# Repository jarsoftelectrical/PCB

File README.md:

# PCB
PCB files for various projects

Some of these have not been prototyped and may have faults, use at your own risk.

Created with Eagle CAD  full version, any changes please share back to me.

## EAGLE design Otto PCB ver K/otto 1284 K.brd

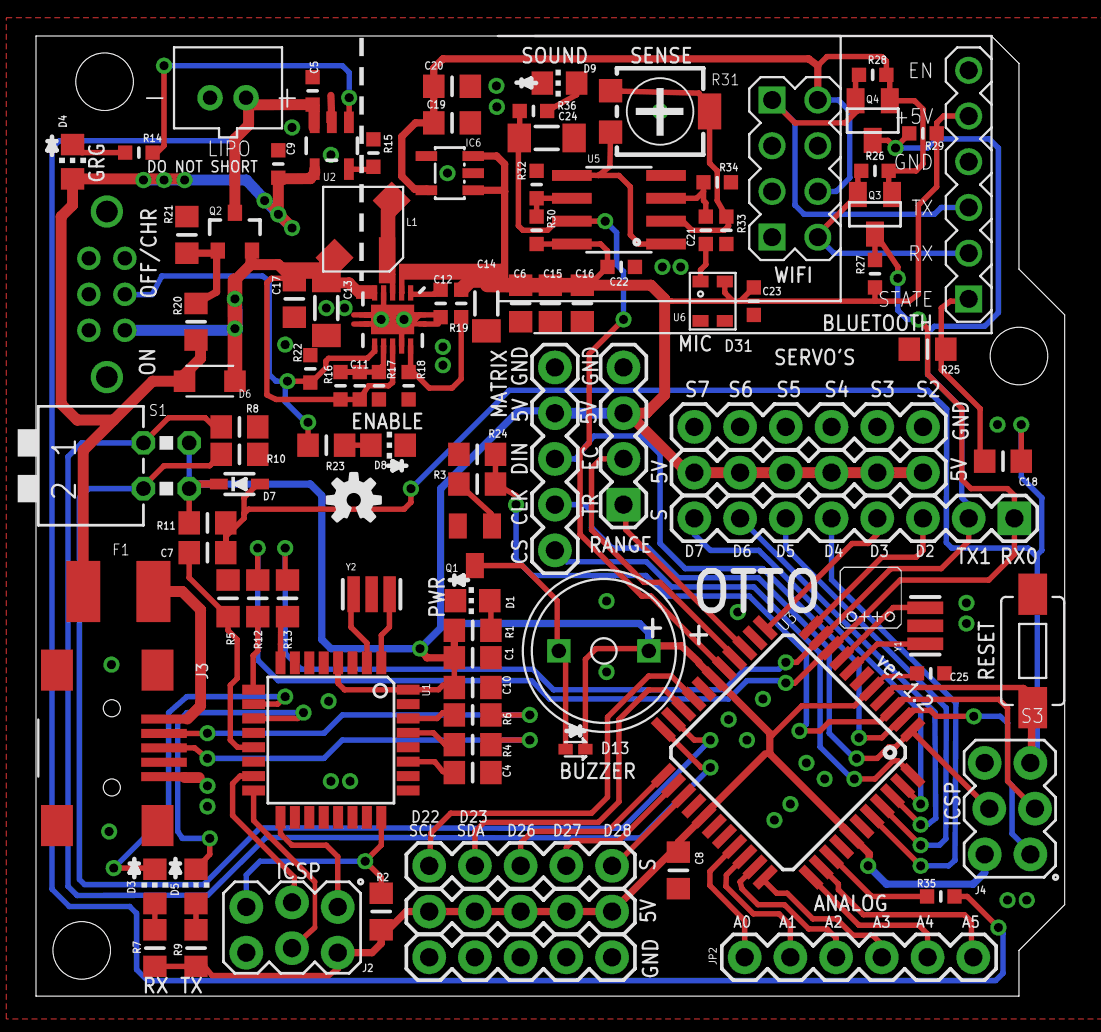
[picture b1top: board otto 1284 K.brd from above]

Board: 2 copper layers, 57.2 x 53.3 mm, 104 parts (0 on the bottom side), 79 nets.

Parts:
C1, C7, C8, C10, C18, C20: 0.1u; C0805MP
C4: 1u; C0805MP
C5, C9: 4.7uF; C0603MP
C6, C15, C16, C17, C19: 22uF; C0805MP
C11, C12, C21: 0.1uF; C0603MP
C13, C14, C24: 10uF; C1206MP
C22, C23, C25: 0.1u; C0603MP
D1: PWR (Green); CHIP-LED0805MP
D2: PMEG2010AEB,115; SOD-523
D3: RX (Yellow); CHIP-LED0805MP
D4: CHRGE(RED); CHIP-LED0805MP
D5: TX (Yellow); CHIP-LED0805MP
D6: PMEG3010BER; SOD123W
D7: ZHCS400TC; SOD323
D8: EN (Green); CHIP-LED0805MP
D9: SOUND(RED); CHIP-LED0805MP
F1: MF-MSMF050-2 500mA; L1812
IC6: LP2985-33DBVR; SOT23-DBV
J2, J4: 3x2 MALE HEADER; 2X03_LOCK
J3: USB-MINI-B_2
JP1, JP2, JP4: 6x1 MALE HEADER; 1X06
JP3: 8x1 MALE HEADER; 1X08
JP5, JP7, JP8, JP9: 5x1 MALE HEADER; 1X05
JP6: 4x1 MALE HEADER; 1X04
L1: 4.7uH, 1.2A; INDUCTOR-CDRH4D16FB
LIPO: JST-PH-2-THM
LOGO2: OSHW-LOGOS; OSHW-LOGO-S
Q1, Q3, Q4: 2N7002; SOT23
Q2: DMP2305U; SOT23-3
R1, R7, R9, R12, R13, R23: 1k; R0805MP
R2, R5, R11, R20, R25: 10k; R0805MP
R3: 680R; R0805MP
R4, R6: 22R; R0805MP
R8, R10, R21, R24: 100k; R0805MP
R14: 470; R0603MP
R15: 2k; R0603MP
R16, R19: 2M; R0603MP
R17, R18: 220k; R0603MP
R22: 100k; R0603MP
R26, R27, R28, R29: 10K; R0603MP
R30: 6k8; R0603MP
R31: 100K; RTRIM4G/J
R32: 3K3; R0603MP
R33, R36: 1K; R0603MP
R34: 100K; R0603MP
R35: 1M; R0603MP
S1: MCDA02; DA-02
S2: EG2211
S3: SWITCH-MOMENTARY-2-SMD-1101NE; TACTILE-SWITCH-1101NE
SG1: BUZZER-TMB09A05; BUZZER_9MM_PTH
U1: ATMEGA8U2AU; TQFP32-08
U2: MCP73831; SOT23-5
U3: ATMEGA1284AU; TQFP44
U4: TPS61200; QFN-10_PAD
U5: LMV358; SO08
U6: SPW2430_SILICON_MIC
U$1: 6x1 FEMALE HEADER; WIRELESS-BLUETOOTH-HC-05-PLAIN
U$2: 4x2 FEMALE HEADER; WIRELESS-WIFI-ESP-01-PLAIN
U$47: SHIELDSMALL; ARDUINOSHIELDSMALL
Y1, Y2: 16MHz; RESONATOR

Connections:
+3V3: C19.1, C20.1, IC6.5, Q3.1, Q4.1, R26.2, R28.2, U$2.B2, U$2.D2
A0: JP2.1, U3.30
A1: JP2.2, U3.31
A2: JP2.3, U3.32
A3: JP2.4, U3.33
A4: JP2.5, U3.34
A5: JP2.6, U3.35
A6: R35.2, U3.36
BOOSTEN: R22.1, R23.2, S2.P2, U4.6
D0: JP3.1, Q3.3, R12.1, R27.1, U3.9
D1: JP3.2, Q4.3, R13.1, R29.1, U3.10
D2: JP3.3, U3.11
D3: JP3.4, U3.12
D4: JP3.5, U3.40
D5: JP3.6, U3.41
D6: JP3.7, U3.42
D7: JP3.8, U3.43
D8: JP6.1, U3.14
D9: JP6.2, U3.15
D10: JP5.1, U3.44
D24: R10.1, S1.2, U3.21
D25: R8.1, S1.1, U3.22
D26: JP7.3, U3.23
D27: JP7.4, U3.24
D28: JP7.5, U3.25
D+: R4.2, U1.29
D-: R6.2, U1.30
FB: R18.2, R19.1, U4.10
GND: C1.2, C4.2, C5.2, C6.2, C8.2, C9.2, C10.2, C12.2, C13.2, C14.2, C15.2, C16.2, C17.2, C19.2, C20.2, C22.2, C23.2, C24.2, C25.2, D1.C, D8.C, D9.C, IC6.2, J2.6, J3.1, J3.6, J3.7, J3.8, J3.9, J4.6, JP4.1, JP4.2, JP4.3, JP4.4, JP4.5, JP4.6, JP5.5, JP6.4, JP9.1, JP9.2, JP9.3, JP9.4, JP9.5, LIPO.2, Q1.2, R5.1, R8.2, R10.2, R15.2, R17.1, R18.1, R21.2, R22.2, R24.1, R25.1, R32.2, R33.2, R34.2, S2.P2-TA, S3.P$2, U1.3, U1.28, U2.2, U3.6, U3.18, U3.28, U3.39, U4.4, U4.9, U4.11, U4.12, U4.13, U4.14, U4.15, U5.4, U6.2, U6.3, U$1.4, U$2.A1, Y1.2, Y2.2
MISO: J4.1, JP5.3, U3.2
MOSI: J4.4, JP5.2, U3.1
unnamed: U3.8, Y1.3
unnamed: U3.7, Y1.1
unnamed: R15.1, U2.5
unnamed: D2.A, Q1.3, SG1.P$1
unnamed: Q1.1, R3.1
unnamed: R12.2, U1.9
unnamed: R13.2, U1.8
unnamed: U1.1, Y2.3
unnamed: U1.2, Y2.1
unnamed: C4.1, U1.27
unnamed: J3.3, R4.1
unnamed: J3.4, R6.1
unnamed: J2.1, U1.17
unnamed: J2.3, U1.15
unnamed: J2.5, R2.1, U1.24
unnamed: J2.4, U1.16
unnamed: F1.2, J3.5
unnamed: R14.1, U2.1
unnamed: D4.C, R14.2
unnamed: L1.P$1, U4.3
unnamed: C12.1, U4.1
unnamed: D8.A, R23.1
unnamed: C18.1, R25.2, U$1.1
unnamed: Q2.1, R20.2, R21.1
unnamed: R31.1, R31.2, R33.1, U5.2
unnamed: D3.A, R7.1
unnamed: D5.A, R9.1
unnamed: R31.3, U5.1, U5.5
unnamed: D3.C, U1.10
unnamed: D5.C, U1.11
unnamed: C7.2, R5.2, U1.13
unnamed: R30.2, R32.1, U5.6
unnamed: C21.2, R34.1, U5.3
unnamed: D1.A, R1.1
unnamed: C21.1, U6.1
unnamed: D9.A, R36.2
RESET: C7.1, C18.2, D7.A, J4.5, R11.1, S3.P$1, U3.4
SCK: J4.3, R3.2, R24.2, U3.3
SCL: JP7.1, U3.19
SDA: JP7.2, U3.20
SOUND: C24.1, R36.1, U3.16, U5.7
UVLO: C11.2, R16.1, R17.2, U4.7
VBATT: C5.1, LIPO.1, Q2.3, R35.1, U2.3
VBOOSTIN: C11.1, C13.1, C17.1, D6.1, L1.P$2, Q2.2, R16.2, S2.P2-TB, U4.5, U4.8
VCC: C1.1, C6.1, C8.1, C10.1, C14.1, C15.1, C16.1, C22.1, C23.1, C25.1, D2.C, D7.C, IC6.1, IC6.3, J2.2, J4.2, JP1.1, JP1.2, JP1.3, JP1.4, JP1.5, JP1.6, JP5.4, JP6.3, JP8.1, JP8.2, JP8.3, JP8.4, JP8.5, R1.2, R2.2, R7.2, R9.2, R11.2, R19.2, R27.2, R29.2, R30.1, S1.3, S1.4, SG1.P$2, U1.4, U1.32, U3.5, U3.17, U3.27, U3.38, U4.2, U5.8, U6.4, U$1.5
VUSB: C9.1, D4.A, D6.2, F1.1, R20.1, U2.4
WIFIRX: Q4.2, R28.1, U$1.3, U$2.D1
WIFITX: Q3.2, R26.1, U$1.2, U$2.A2

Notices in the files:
parts and their libraries:
rc-master-smd: Copyright (C) 2007-2008, Bob Starr
SparkFun-Connectors: Licensing: CC v3.0 Share-Alike You are welcome to use this library for commercial purposes.
diy-modules: Released under the Creative Commons Attribution 4.0 International License: http://creativecommons.org/licenses/by/4.0
